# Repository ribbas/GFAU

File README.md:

<div align="center">
  
</div>

## Galois Field Arithmetic Unit

This project will produce a hardware-based unit for performing arithmetic operations in Galois Field 2<sup>n</sup>, where n = 2…10. Unit will accept inputs to determine n, and to establish the field generating polynomial. A GFAU would serve as a computation engine for a relatively low-powered microcontroller, and would enable complex code and encryption algorithms. Project will include implementation of a Reed Solomon encoder and decoder using the GFAU.

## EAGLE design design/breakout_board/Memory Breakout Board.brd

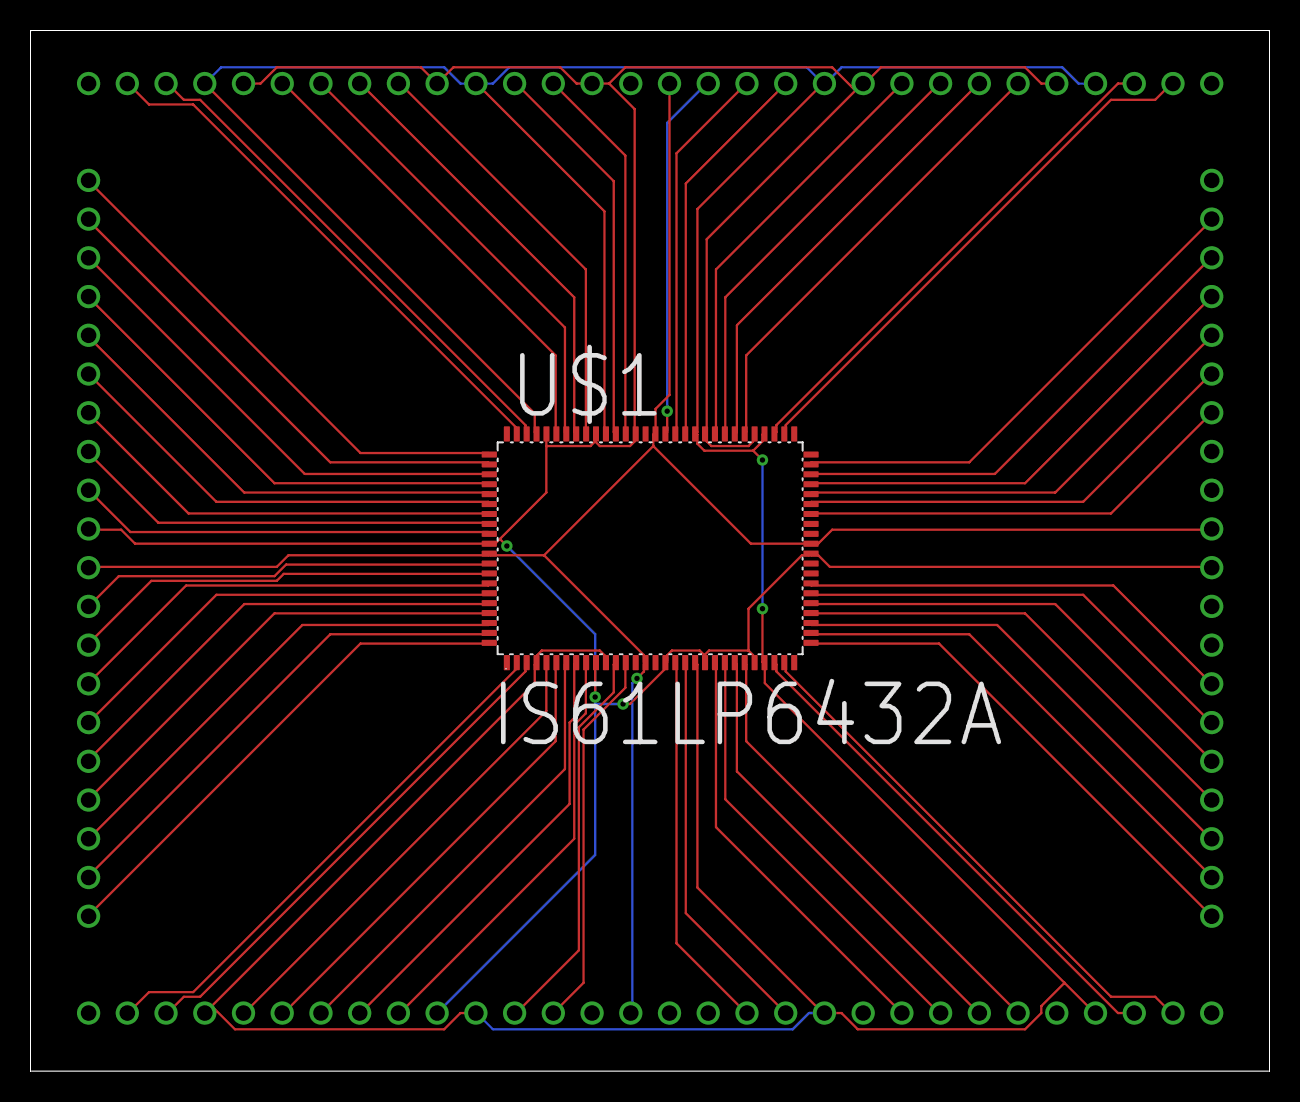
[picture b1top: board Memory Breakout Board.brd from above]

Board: 2 copper layers, 81.3 x 68.2 mm, 5 parts (0 on the bottom side), 68 nets.

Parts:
U$1: IS61LP6432A
U$2, U$3: HEADER20
U$4, U$5: HEADER30

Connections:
A6: U$1.100, U$3.P$20
A7: U$1.99, U$3.P$19
A8: U$1.82, U$3.P$2
A9: U$1.81, U$3.P$1
ADSC: U$1.85, U$3.P$5
ADSP: U$1.84, U$3.P$4
ADV: U$1.83, U$3.P$3
BW1: U$1.93, U$3.P$13
BW2: U$1.94, U$3.P$14
BW3: U$1.95, U$3.P$15
BW4: U$1.96, U$3.P$16
BWE: U$1.87, U$3.P$7
CE: U$1.98, U$3.P$18
CE2: U$1.97, U$3.P$17
CLK: U$1.89, U$3.P$9
DBQ8: U$1.79, U$5.P$29
GW: U$1.88, U$3.P$8
unnamed: U$1.2, U$4.P$2
unnamed: U$1.3, U$4.P$3
unnamed: U$1.31, U$2.P$1
unnamed: U$1.5, U$4.P$5
unnamed: U$1.6, U$4.P$6
unnamed: U$1.7, U$4.P$7
unnamed: U$1.8, U$4.P$8
unnamed: U$1.9, U$4.P$9
unnamed: U$1.32, U$2.P$2
unnamed: U$1.12, U$4.P$12
unnamed: U$1.13, U$4.P$13
unnamed: U$1.18, U$4.P$18
unnamed: U$1.19, U$4.P$19
unnamed: U$1.22, U$4.P$22
unnamed: U$1.23, U$4.P$23
unnamed: U$1.24, U$4.P$24
unnamed: U$1.25, U$4.P$25
unnamed: U$1.28, U$4.P$28
unnamed: U$1.29, U$4.P$29
unnamed: U$1.33, U$2.P$3
unnamed: U$1.4, U$1.11, U$1.20, U$1.27, U$1.54, U$1.61, U$1.70, U$1.77, U$4.P$4, U$4.P$11, U$4.P$20, U$4.P$27, U$5.P$4, U$5.P$11, U$5.P$20, U$5.P$27
unnamed: U$1.34, U$2.P$4
unnamed: U$1.35, U$2.P$5
unnamed: U$1.36, U$2.P$6
unnamed: U$1.37, U$2.P$7
unnamed: U$1.44, U$2.P$14
unnamed: U$1.45, U$2.P$15
unnamed: U$1.46, U$2.P$16
unnamed: U$1.47, U$2.P$17
unnamed: U$1.48, U$2.P$18
unnamed: U$1.49, U$2.P$19
unnamed: U$1.52, U$5.P$2
unnamed: U$1.53, U$5.P$3
unnamed: U$1.56, U$5.P$6
unnamed: U$1.57, U$5.P$7
unnamed: U$1.58, U$5.P$8
unnamed: U$1.59, U$5.P$9
unnamed: U$1.62, U$5.P$12
unnamed: U$1.63, U$5.P$13
unnamed: U$1.64, U$5.P$14
unnamed: U$1.68, U$5.P$18
unnamed: U$1.69, U$5.P$19
unnamed: U$1.72, U$5.P$22
unnamed: U$1.73, U$5.P$23
unnamed: U$1.74, U$5.P$24
unnamed: U$1.75, U$5.P$25
unnamed: U$1.78, U$5.P$28
OE: U$1.86, U$3.P$6
VDD: U$1.15, U$1.41, U$1.65, U$1.91, U$2.P$11, U$3.P$11, U$4.P$15, U$5.P$15
VSS: U$1.10, U$1.17, U$1.21, U$1.26, U$1.40, U$1.55, U$1.60, U$1.67, U$1.71, U$1.76, U$1.90, U$2.P$10, U$3.P$10, U$4.P$10, U$5.P$5, U$5.P$10, U$5.P$17, U$5.P$21, U$5.P$26
_CE2: U$1.92, U$3.P$12

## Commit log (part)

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2017-09-26 add basic git how to, revert contract.tex to Howard and Brian's versions
2017-09-27 add scanned contract
2017-10-01 add files from Drive
2017-10-01 Add files via upload
    Added LaBerge's GFAU ppt slide.
2017-10-02 update template latex file
2017-10-03 Added Capstone schedule
2017-10-04 Added Team Status Report Template
2017-10-06 reorganize repo, add tsr01.tex
2017-10-07 update background doc
2017-10-10 Added SRR requirements and rubric
2017-10-13 start on specs draft
2017-10-15 restructure repo, add logo
2017-10-15 fix math in markdown, organize team_docs
2017-10-18 Added System Boundary Diagram.png
2017-10-19 update srs_draft, GUYS WE'RE ALMOST DONE
2017-10-19 Added TSR02
2017-10-20 Added Team Schedule
2017-10-20 reducibility check
2017-10-20 reducibility test waveforms added
2017-10-20 Added LaBerge's schedule
2017-10-21 Updated TSR02 again
2017-10-21 update gitignore, add VHDL manual, organize repo, update background SDD
2017-10-21 update maths for one-cycle operations
2017-10-22 add multiplication analytical equation
2017-10-23 add division analytical equation
2017-10-23 compressed FPGA slides, update background analytics on multiplication
2017-10-27 i think memory works
2017-10-27 init mem_test and update background
2017-11-01 update structure.tex, add sow template
2017-11-02 Updated SOW
2017-11-02 added schematic, opcode table
2017-11-03 start carrylookahead adder
2017-11-04 add tsr03
2017-11-06 add copy of srs draft as template for final
2017-11-08 restructure repo, major update to background
2017-11-13 add partial full and carry lookahead structural adders
2017-11-13 update background, begin working on claadder
2017-11-17 add feedback of SRS and SOW drafts, major update to background, add algorithms for mult and div
2017-11-20 rename docs, update SRS, add structural claadder4 and 16
2017-11-23 finish initial draft of srs_final
2017-11-26 add list of modules
2017-11-27 Rename modules.md to README.md
2017-11-27 Sabbir fixed the claadder16 all by himself
2017-11-27 Jeffrey fixed the claadder16
2017-11-27 implement mul16 with hardcoded MSBs
2017-11-29 2's Complement
2017-11-29 two's complement works, but zero padding synthesizes to a supercomputer
2017-12-01 polish up SOW draft for final draft
2017-12-01 add pdr instructions
2017-12-01 sow final proofed and edited slightly by brian
2017-12-06 new pdr diagrams
2017-12-07 copy tsr04 to repo
2017-12-15 add clock to tb, attempt state machine
2017-12-16 convert integers to std logic
2017-12-16 add synthesizable size module
2017-12-16 update background math on division, add synthesizable div
2017-12-16 reorganize modules, add tb for addsub16
2017-12-17 start outofboundexception
2017-12-17 finish outofboundsexception lol
2017-12-17 optimize boundhandler, start on zero checker
2017-12-18 outselect_tb uploaded
2017-12-18 update list of modules
2017-12-20 convert mul16 to synchronous
2017-12-20 update math background with 15 degree polynomials
2018-01-02 add synchronous version of mul16 as a prototype
2018-01-04 Control Unit update
2018-01-04 polished up mul16
2018-01-05 clean up whitespace, reorganize cu modules
2018-01-05 reorganize modules, start automatic symbols
2018-01-06 add automatic symbol generator
2018-01-06 add synchronous version of symbol generator
2018-01-06 add list of primitive polynomials
2018-01-06 add single symbol generator
2018-01-07 update background on primitive polynomials
2018-01-08 finish polynomial generator
2018-01-09 attempt 'concurrent' term generation
2018-01-09 add broken parallel symbol generator
2018-01-10 begin top with test signals
2018-01-11 modularize maskedtc out of div to reduce complexity, add temporary signals in top_tb
2018-01-11 add more test signals to top, refactor CLA adder, remove structural mods
2018-01-11 fix outselect
2018-01-12 modularize operators away into top
2018-01-12 add enable to generator
2018-01-13 begin adding CU to top
2018-01-13 adding arithmetic exceptions to CU
2018-01-13 add out of bound and zero exception to CU
2018-01-13 finish integrating CU into top
2018-01-16 add doc headers
2018-01-16 add memory lookup
2018-01-17 add full case to control unit
2018-01-17 add zero_err support for all operations
2018-01-22 revert zero flags for add/sub in CU
2018-01-22 rename isnull, attempt second layer of control unit in handling zero
2018-01-24 integrate null exception into output mux
2018-01-25 move mem wrapper out of operators
2018-01-25 add draw.io schematic
2018-01-30 update block schematic
2018-01-30 finish most of block schematic
2018-01-31 breakout board files added
2018-01-31 fix merge conflict on block diagram
2018-01-31 add URCAD abstract guideline and template
2018-02-01 add primitive checker script
2018-02-02 finish and documented isprimitive
2018-02-02 add module todos, fix operators tb
2018-02-06 add URCAD abstract draft
2018-02-09 Added TSR 06
2018-02-09 board just needs silk screen layer
2018-02-10 Updated tsr06
2018-02-10 Fixed typo
2018-02-20 update URCAD abstract
2018-02-24 submit URCAD abstract
2018-02-24 add primpoly to exclude requirement for MATLAB
2018-02-24 removing deprecated files
2018-02-24 moving breakout files to a deprecated feature branch
2018-02-24 add helper scripts to generate list of all primitive polynomials
2018-02-24 modularized process for generating list of primitive polynomials for n degree
2018-02-24 restructure C scripts
2018-03-01 Added CDR instruction
2018-03-01 getting back on track with this fucking vhdl
2018-03-08 consolidate all presentations
2018-03-08 add temporary list of fixed bitvector counts to be parameterized
2018-03-08 Memory vhdl modules
2018-03-09 Updated Block Diagrams
2018-03-09 fuckdnfkjdsnfkjbsdfk
2018-03-09 tsr08
2018-03-09 tsr07
2018-03-10 refactor isbounded, replace ports in CU with 9 bits
2018-03-10 almost done with UML
2018-03-10 add generator to UML
2018-03-10 optimize the poop out of generator
2018-03-11 add generics to ALU and CU mods
2018-03-11 rename all OPS
2018-03-17 add presentation PDFs
2018-03-22 parameterize gen mods
2018-03-23 parameterize and test with sync ops, generate their synthesis reports
2018-03-23 remove temporary logs
2018-03-23 parameterize all ops mods
2018-03-23 add parameterized ops to top ops mod
2018-03-23 remove unnecessary ports and mods
2018-03-29 parameterized all operators and outselect, time to fuck with memory
2018-03-29 update diagrams
2018-03-29 add state machines to memory wrapper
2018-03-31 remove constant ports from mem wrapper
2018-03-31 add demo pkg to hold all constants, design is now modular af
2018-03-31 add constants for test benches, minor refactor
2018-03-31 begin integrating ops
2018-04-01 move state types to package header
2018-04-01 begin integrating new memory wrapper with cu
2018-04-01 parameterize and update top
2018-04-01 update docs
2018-04-05 add separate ports to mem wrapper
2018-04-05 attempt to convert gen into async
2018-04-05 reduce size of poly_bcd by 1 bit (yay!)
2018-04-07 add updated gen with the mixed triggers
2018-04-09 organize diagrams from statics
2018-04-09 update functional flow diagram
2018-04-11 update the old-ass deprecated data flow diagram we've been using forever
2018-04-11 finish block schematic and system boundary diagrams
2018-04-12 increase font size for system boundary
2018-04-13 add first draft of poster
2018-04-13 added IO handler info. Still need to update timing diagram
2018-04-13 Updated generator null bits
2018-04-13 i fucked up
2018-04-15 update system block schematic
2018-04-15 update poster ppt
2018-04-16 increase font size in block schematic
2018-04-20 updated interface info
2018-04-20 added IO blurbs in new poster
2018-04-20 updated memory.vhd to correctly write to memory. still need to update reading. Not sure how to check syntax. May be able to use IODELAY2 primitive to delay control signals instead of writing over 2 c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
2018-04-20 finished read i think. probably still broken since idk how to syntax check outside a xilinx project
2018-04-21 add customized waveforms for poster
2018-04-21 integrate memory wrapper into cu for only add/sub
2018-04-21 fix minor syntax errors on mem_wrapper and io_port
2018-04-22 finish poster
2018-04-22 add handout material
2018-04-27 separete log for future addition of multiplicative inverses
2018-04-27 completely refactor generator with less hardware and code
2018-04-28 move memory package to deprecated
2018-04-28 update poster waveforms
2018-04-29 refactor top with updated modules, cu, gen and ops seem to work fine
2018-04-29 add enable to outconvert, almost implement rdyout
2018-04-29 add enable to cu, ops and con, implement rdyout, top synthesizes
2018-05-01 update poster for final presentation
2018-05-03 remove ununsed bits from registers
2018-05-03 renamed tsr
2018-05-03 added mem_rdy
2018-05-03 add mem_rdy back lol
2018-05-03 remove unnecessary signals from sensitivity list of mem
2018-05-03 yay top works nice with gen and mem
2018-05-03 connect mem_t_con to operators
2018-05-03 fix top lol
2018-05-03 rename demo.vhd, almost done with python module generator
2018-05-04 polish up that dynamic module generator, organize modules
2018-05-04 fix modgen
2018-05-04 fix outconvert
2018-05-04 adding flippity floppity inside gen
2018-05-04 added my own SHIT
2018-05-05 found bug in mem_wrapper when writing data
2018-05-07 add demo rubric
2018-05-07 added master reset
2018-05-07 add master reset port to ops, kind of useless atm
2018-05-07 IO handler FSM working, need to edit deserialize for receiving generating polynomials, and make top module
2018-05-09 change the backgroun doc thingy to sdd pretty much
2018-05-09 remove flippity flop from mem_wrapper like it should be, start gen v999.9.1
2018-05-09 added a quick module to handle flipping
2018-05-09 add all pins to ucf
2018-05-10 make python script purdy
2018-05-10 almost done with sdd - first update since January
2018-05-10 move all deprecated files to its feature branch to begin cleanup of repo
2018-05-10 updated directories
2018-05-10 update master reset warnings
2018-05-10 fix cu with master reset
2018-05-10 begin integrating IO into top
2018-05-10 sorry for the mess lol
2018-05-10 revert polybcd back to n bits
2018-05-10 add Sabbir's ISE files
2018-05-10 no more io handler warnings
2018-05-11 io port should work
2018-05-11 io should work now
2018-05-11 top finally synthesizes...for now
2018-05-11 moved fixed io_handler files
2018-05-11 updated mods directory
2018-05-11 UHHHHH
2018-05-11 UHHHHHHgit add -A git add -A git add -A !
2018-05-11 bring warnings down to 32, edit ports of indices
2018-05-11 eggggggggggghhhhhhhhhhhhhhhhhhhhhhhhhhhh
2018-05-11 some arduino stuff is added
2018-05-11 add arduino pins to ucf
2018-05-11 add temporary mode port
2018-05-12 begin fixing data vector sizes
2018-05-12 fix bit issue in gen
2018-05-12 fix bit sizes in ops, no warnings so far
2018-05-12 reduce warnings in mem, left with 16 easy-fix warnings in unconnected ports, 11 others
2018-05-12 synchronized tclk with clk. Programming file generates without only one negligable warning
2018-05-13 we need to clean up these files @brian
2018-05-14 remove duplicates and unnecessary ISE files
2018-05-14 fix MOST warnings with gen
2018-05-14 move nth elem to a latch
2018-05-14 convert enable in cu to latch
2018-05-15 remove duplicate modules
2018-05-15 add master top
2018-05-16 added updated arduino file
2018-05-16 add signals to top_tb, no idea how to get the proper data in on time
2018-05-16 top_tb looks a little more accurate, but I can't keep brute forcing this
2018-05-16 working hardware testing
2018-05-16 testing with operation opcodes
2018-05-16 revert indices to re-include priority encoder for deg
2018-05-16 ucf file
2018-05-16 redo cu
2018-05-17 idk lol
2018-05-17 bin file
2018-05-18 working out hardware bugs
2018-05-18 re-integrate arithmetic exceptions with less hardware
2018-05-18 remove extraneous constants
2018-05-19 fix ismember mod
2018-05-19 add simple sample parser thingy
2018-05-20 generator now synchronizes with the right value of flip
2018-05-20 synthesis worked on vivado (xilinx error messages were garbage)
2018-05-20 giving up for today... can't get memory to work. everything else does though
2018-05-22 i guess this is it :/
2018-05-22 sad :'''(
